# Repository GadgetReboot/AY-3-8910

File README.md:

# AY-3-8910
AY-3-8910 Sound Generator PCB controlled by Arduino Nano<BR><BR>
<br><br>

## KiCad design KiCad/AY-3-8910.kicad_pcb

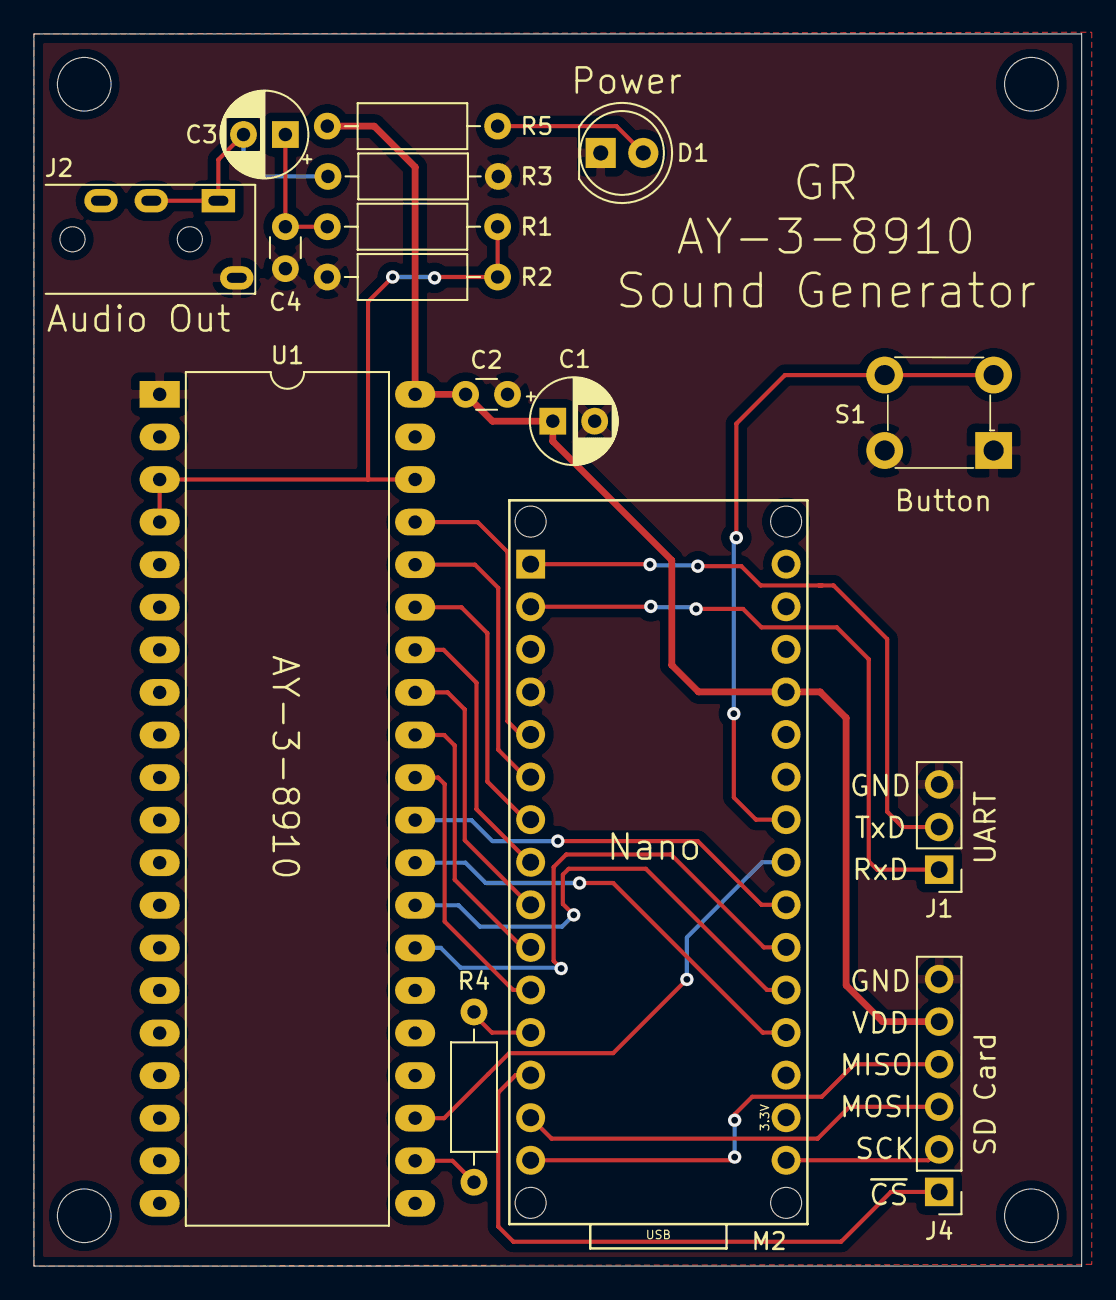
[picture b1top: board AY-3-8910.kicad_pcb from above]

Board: 2 copper layers, 62.5 x 73.5 mm, 20 parts (0 on the bottom side), 27 nets.

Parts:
C1, C3: 1uF; CP_Radial_D5.0mm_P2.50mm
C2: 100nF; C_Disc_D3.0mm_W1.6mm_P2.50mm
C4: 4.7nF; C_Disc_D3.0mm_W1.6mm_P2.50mm
D1: LED_Small_ALT; LED_D5.0mm
J1: UART; PinHeader_1x03_P2.54mm_Vertical
J2: AudioJack4; Jack_3.5mm_PJ320A_Horizontal
J4: Conn_01x06; PinHeader_1x06_P2.54mm_Vertical
M2: Arduino_Nano_Socket
MH1, MH2, MH3, MH4: MountingHole; MountingHole_3.2mm_M3
R1: 4.7K; R_Axial_DIN0207_L6.3mm_D2.5mm_P10.16mm_Horizontal
R2: 1K; R_Axial_DIN0207_L6.3mm_D2.5mm_P10.16mm_Horizontal
R3: 470r; R_Axial_DIN0207_L6.3mm_D2.5mm_P10.16mm_Horizontal
R4: 75r; R_Axial_DIN0207_L6.3mm_D2.5mm_P10.16mm_Horizontal
R5: 300r; R_Axial_DIN0207_L6.3mm_D2.5mm_P10.16mm_Horizontal
S1: 1825910-6; Switch_Tactile_THT_6x6mm
U1: AY-3-8910; DIP-40_W15.24mm_LongPads

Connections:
+5V: C1.1, C2.1, J4.5, M2.5V, R5.1, U1.40
/BC1: M2.A0, U1.29
/BC2: M2.A1, U1.28
/BDIR: M2.A2, U1.27
/CLK: R4.1, U1.22
/DA0: M2.D2, U1.37
/DA1: M2.D3, U1.36
/DA2: M2.D4, U1.35
/DA3: M2.D5, U1.34
/DA4: M2.D6, U1.33
/DA5: M2.D7, U1.32
/DA6: M2.D8, U1.31
/DA7: M2.A3, U1.30
/MISO: J4.4, M2.D12
/MOSI: J4.3, M2.D11
/RxD: J1.1, M2.D0
/SCK: J4.2, M2.D13
/TxD: J1.2, M2.D1
/~CS: J4.1, M2.D10
/~RESET: M2.A4, U1.23
GNDREF: C1.2, C2.2, C4.2, D1.1, J1.3, J2.S, J4.6, M2.GND1, M2.GND2, R2.1, R3.1, S1.1, S1.2, U1.1
unnamed: C3.1, C4.1, R1.1
unnamed: C3.2, J2.R1, J2.T, R3.2
unnamed: D1.2, R5.2
unnamed: M2.A5, S1.3, S1.4
unnamed: M2.D9, R4.2
unnamed: R1.2, R2.2, U1.3, U1.4, U1.38
